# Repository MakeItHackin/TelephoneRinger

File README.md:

# TelephoneRinger

This is a work in progress.... updates and more links to come!
If you have any suggestions, plase let me know by opening an Issue

Project offered under Attribution 4.0 International (CC BY 4.0) License.
  
Not all phone use the same amount of voltage/current to ring.  Seems like the really old phones may require higher wattage and this board may or may not ring them.  
  
BILL OF MATERIALS:
Adafruit Feather (Tested with RP2040, M0 Express, 32u4 Basic, and ESP8266 HUZZAH)  
LEDs 5mm - 3  
RESISTORS 1k - 3  
RJ-11 JACK - 1  
DRV8871 MOTOR CONTROLLER - 1  (https://www.adafruit.com/product/3190)  
XL6019 BOOST CONVERTER - 1  
SWITCHES - 3  
6mm BUTTON - 1  
12mm BUTTON - 3  
  
OPTIONAL:  
RESISTORS 10k - 3  
SSD1306 OLED (i2c) - 1  
FEMALE HEADERS FOR MODULES  
MALE HEADERS FOR MODULES  
LIPO BATTERY - 1
ADAFRUIT FEATHER WING  
TELEPHONE RING GENERATOR PCB

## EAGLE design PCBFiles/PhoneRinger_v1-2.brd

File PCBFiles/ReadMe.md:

PCB Files are a work in progress!

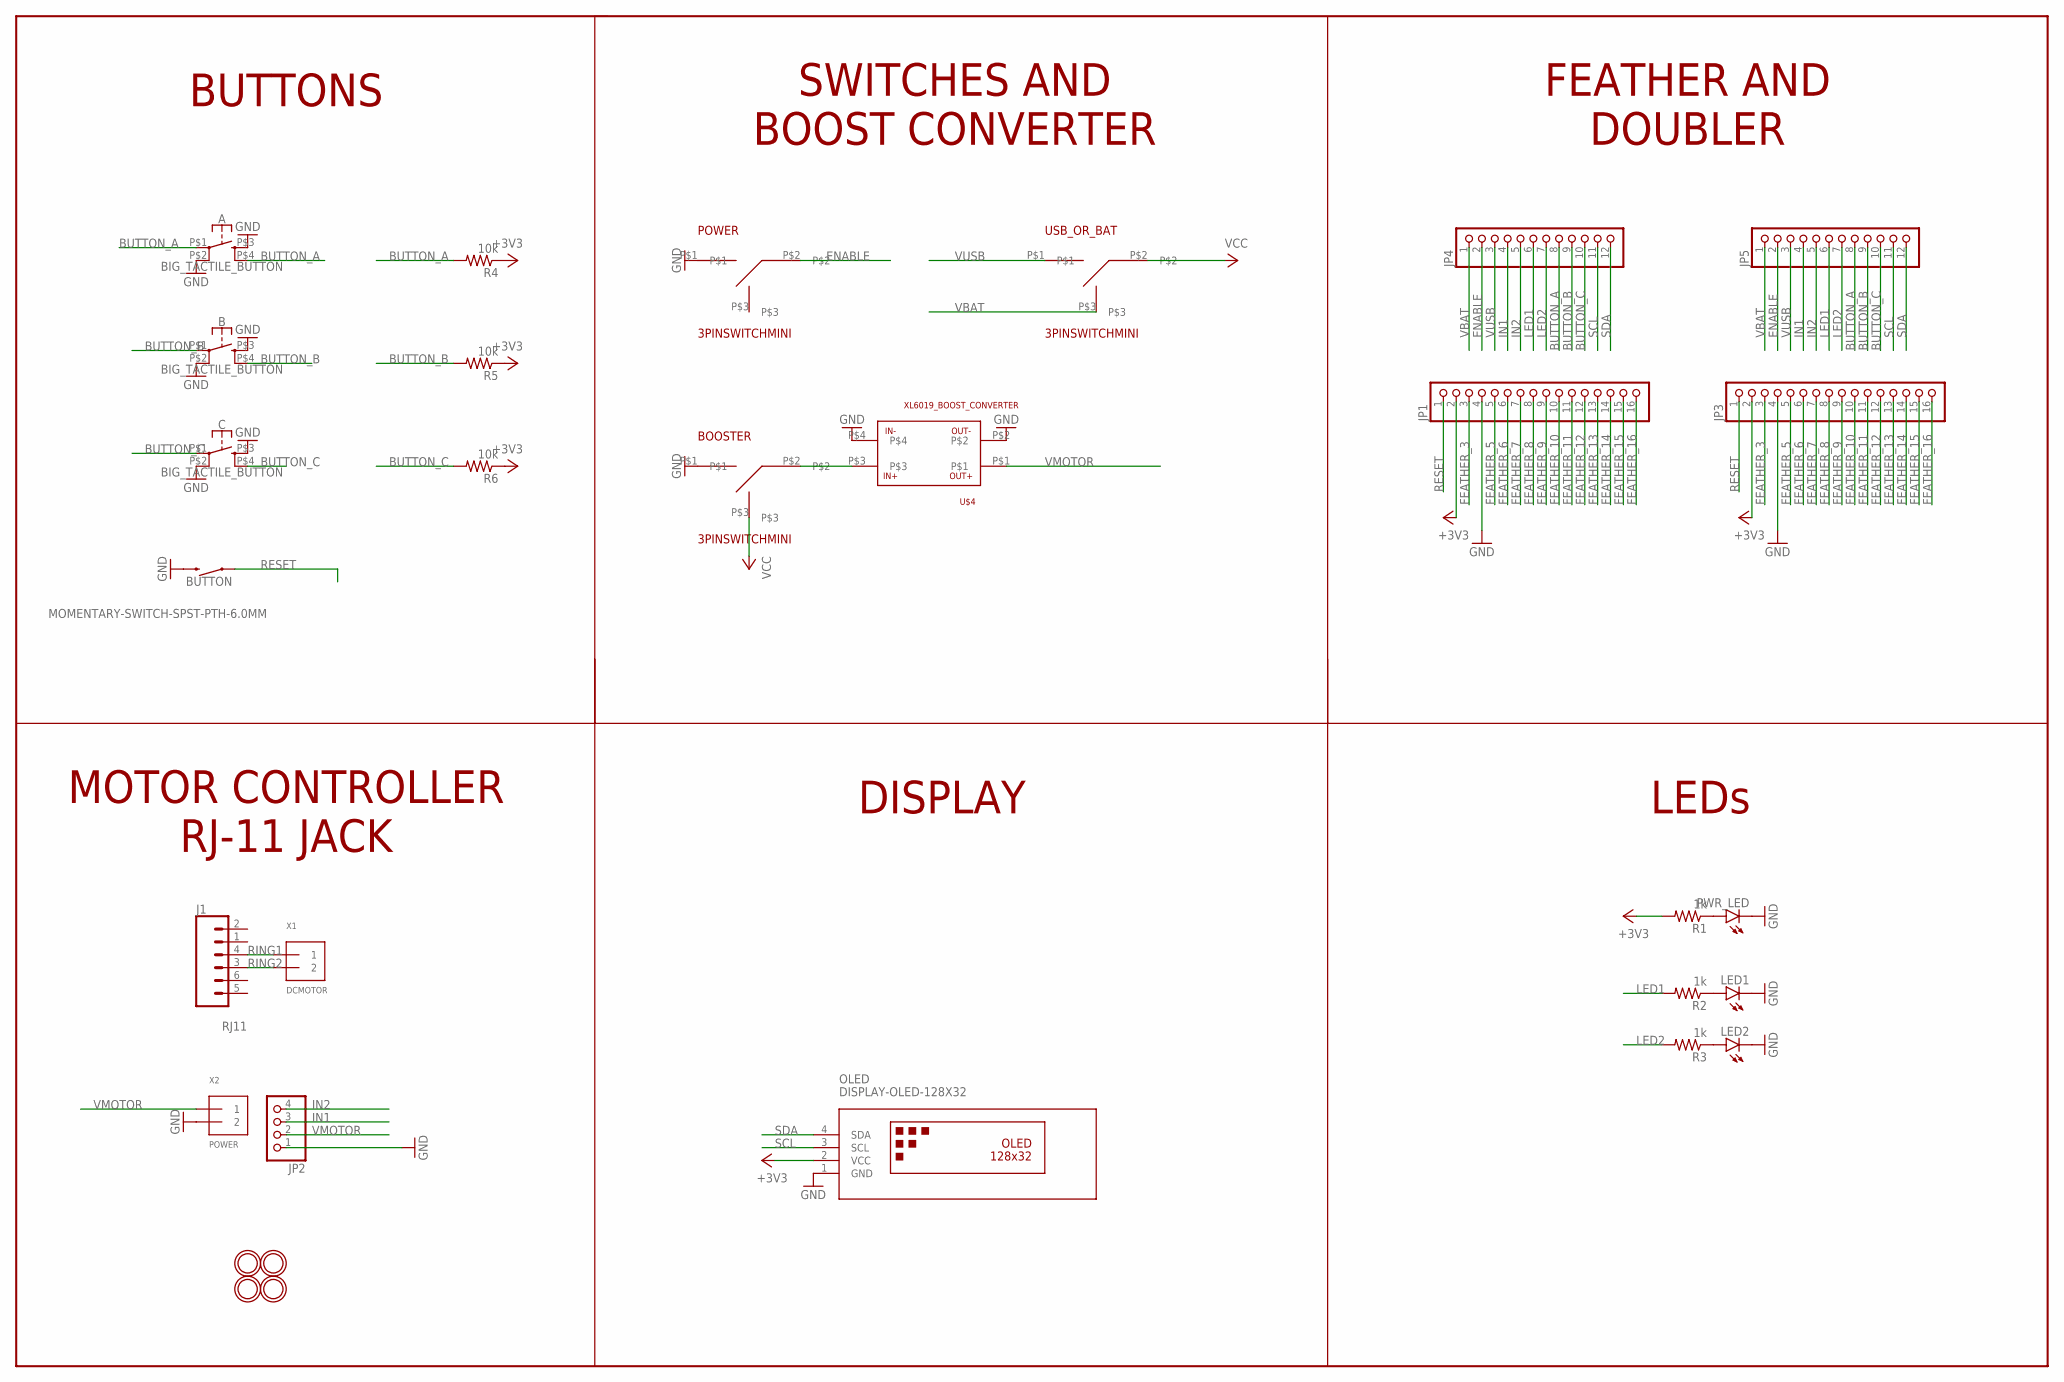
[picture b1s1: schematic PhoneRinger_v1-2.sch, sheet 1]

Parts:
A: BIG_TACTILE_BUTTON; BIG_TACTILE_BUTTON_FP
B: BIG_TACTILE_BUTTON; BIG_TACTILE_BUTTON_FP
BOOSTER: 3PINSWITCHMINI; 3PINMINI
BUTTON: MOMENTARY-SWITCH-SPST-PTH-6.0MM; TACTILE_SWITCH_PTH_6.0MM
C: BIG_TACTILE_BUTTON; BIG_TACTILE_BUTTON_FP
J1: RJ11; RJ11-6
JP1, JP3: HEADER-1X16_76MIL; 1X16_ROUND_76MIL
JP2: HEADER-1X476MIL; 1X04_ROUND_76
JP4, JP5: HEADER-1X1276MIL; 1X12_ROUND_76MIL
LED1, LED2: LED5MM
OLED: DISPLAY-OLED-128X32
POWER: 3PINSWITCHMINI; 3PINMINI
PWR_LED: LED5MM
R1, R2, R3: 1k; 0207/10
R4, R5, R6: 10k; 0207/10
U$4: XL6019_BOOST_CONVERTER; XL6019_FP
U$5, U$6, U$7, U$8: MICROBUILDER_MOUNTINGHOLE2.5_THICK; MICROBUILDER_MOUNTINGHOLE_2.5_PLATED_THICK
USB_OR_BAT: 3PINSWITCHMINI; 3PINMINI
X1: DCMOTOR; TERMBLOCK_1X2-3.5MM
X2: POWER; TERMBLOCK_1X2-3.5MM

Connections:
+3V3: JP1.2, JP3.2, OLED.2 (VCC), R1.2, R4.1, R5.1, R6.1
BUTTON_A: A.P$1 (1), A.P$4 (4), JP4.8, JP5.8, R4.2
BUTTON_B: B.P$1 (1), B.P$4 (4), JP4.9, JP5.9, R5.2
BUTTON_C: C.P$1 (1), C.P$4 (4), JP4.10, JP5.10, R6.2
ENABLE: JP4.2, JP5.2, POWER.P$2
FEATHER_3: JP1.3, JP3.3
FEATHER_5: JP1.5, JP3.5
FEATHER_6: JP1.6, JP3.6
FEATHER_7: JP1.7, JP3.7
FEATHER_8: JP1.8, JP3.8
FEATHER_9: JP1.9, JP3.9
FEATHER_10: JP1.10, JP3.10
FEATHER_11: JP1.11, JP3.11
FEATHER_12: JP1.12, JP3.12
FEATHER_13: JP1.13, JP3.13
FEATHER_14: JP1.14, JP3.14
FEATHER_15: JP1.15, JP3.15
FEATHER_16: JP1.16, JP3.16
GND: A.P$2 (2), A.P$3 (3), B.P$2 (2), B.P$3 (3), BOOSTER.P$1, BUTTON.3 (2), C.P$2 (2), C.P$3 (3), JP1.4, JP2.1, JP3.4, LED1.K (C), LED2.K (C), OLED.1 (GND), POWER.P$1, PWR_LED.K (C), U$4.P$2, U$4.P$4, X2.2
IN1: JP2.3, JP4.4, JP5.4
IN2: JP2.4, JP4.5, JP5.5
LED1: JP4.6, JP5.6, R2.2
LED2: JP4.7, JP5.7, R3.2
unnamed: PWR_LED.A, R1.1
unnamed: LED1.A, R2.1
unnamed: LED2.A, R3.1
unnamed: BOOSTER.P$2, U$4.P$3
RESET: BUTTON.1, JP1.1, JP3.1
RING1: J1.4, X1.1
RING2: J1.3, X1.2
SCL: JP4.11, JP5.11, OLED.3 (SCL)
SDA: JP4.12, JP5.12, OLED.4 (SDA)
VBAT: JP4.1, JP5.1, USB_OR_BAT.P$3
VCC: BOOSTER.P$3, USB_OR_BAT.P$2
VMOTOR: JP2.2, U$4.P$1, X2.1
VUSB: JP4.3, JP5.3, USB_OR_BAT.P$1

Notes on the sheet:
BUTTONS
SWITCHES AND BOOST CONVERTER
FEATHER AND DOUBLER
LEDs
DISPLAY
MOTOR CONTROLLER RJ-11 JACK

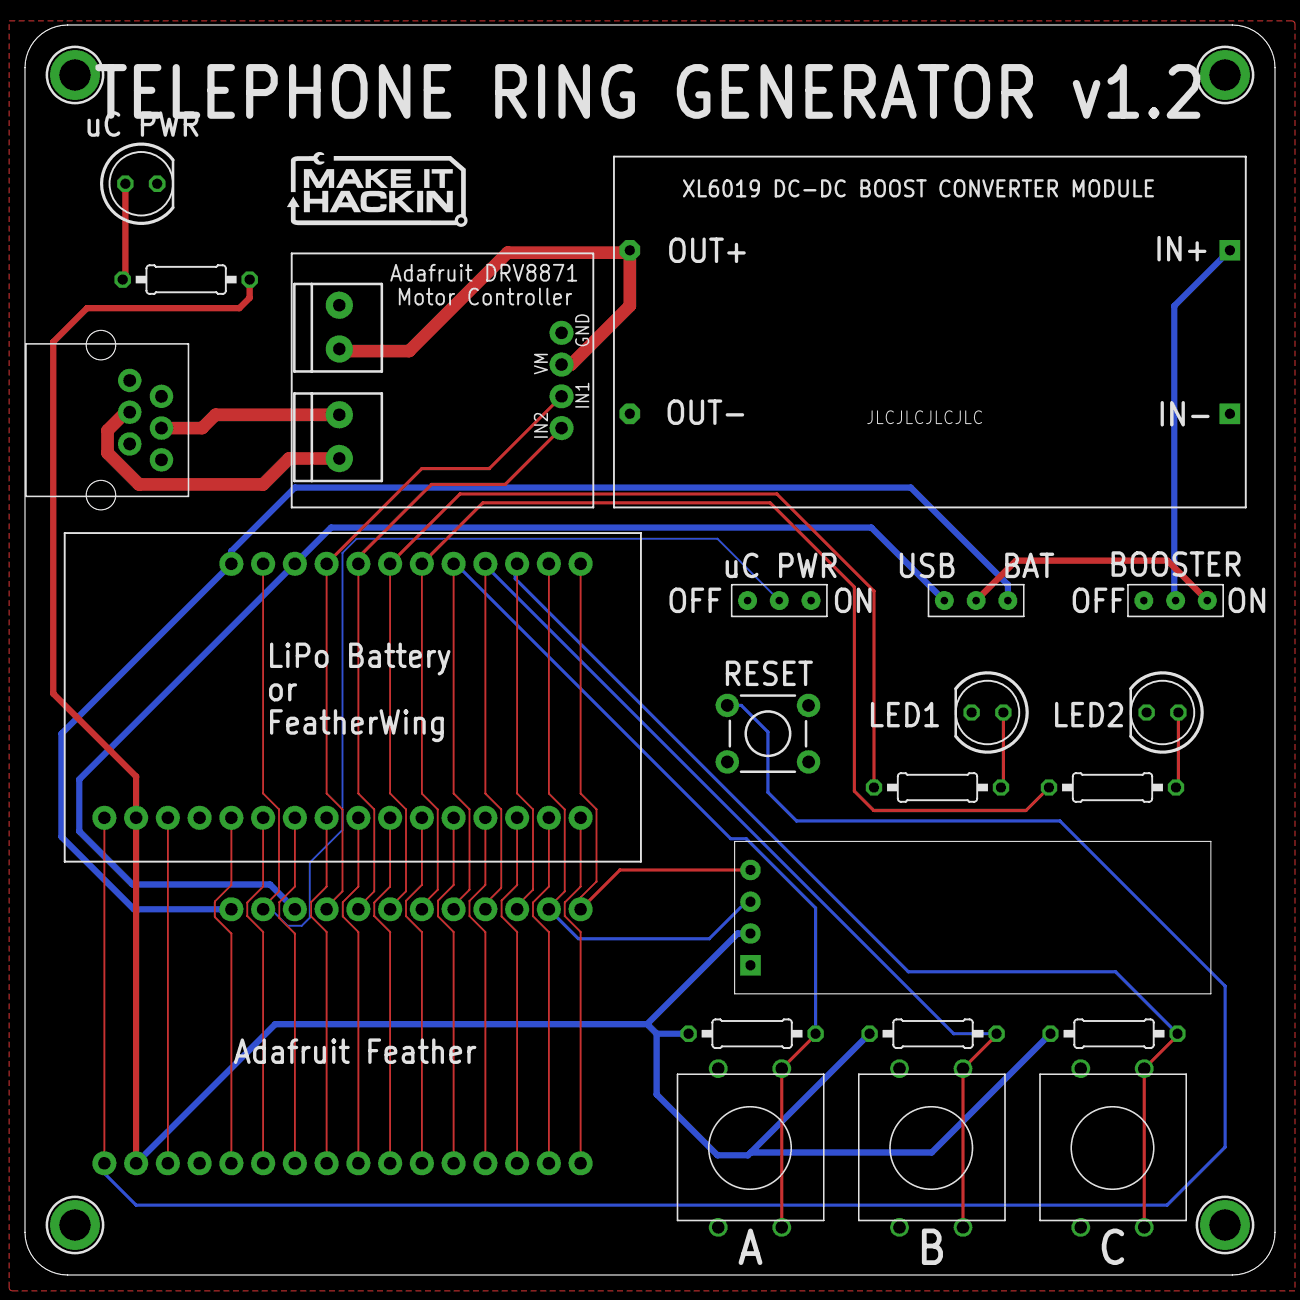
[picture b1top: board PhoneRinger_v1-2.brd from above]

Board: 2 copper layers, 100.0 x 100.0 mm, 30 parts (0 on the bottom side), 36 nets.

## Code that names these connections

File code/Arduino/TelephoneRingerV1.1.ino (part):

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
// PIN ASSIGNMENTS FOR A,B,C BUTTONS, MOTOR CONTROLLER, AND LEDS
#if defined(ESP8266)
  #define BUTTON_A  0
  #define BUTTON_B 16
  #define BUTTON_C  2
  #define IN1 14
  #define IN2 12
  #define LED1 13
  #define LED2 15
#elif defined(ESP32)
  #define BUTTON_A 15
  #define BUTTON_B 32
  #define BUTTON_C 14
  #define IN1 13
  #define IN2 12
  #define LED1 27
  #define LED2 33
#elif defined(ARDUINO_STM32_FEATHER)
  #define BUTTON_A PA15
  #define BUTTON_B PC7
  #define BUTTON_C PC5
  #define IN1 PB5
  #define IN2 PA13
  #define LED1 PA4
  #define LED2 PB4
#elif defined(TEENSYDUINO)
  #define BUTTON_A  4
  #define BUTTON_B  3
  #define BUTTON_C  8
  #define IN1 5
  #define IN2 6
  #define LED1 9
  #define LED2 10
#elif defined(ARDUINO_FEATHER52832)
  #define BUTTON_A 31
  #define BUTTON_B 30
  #define BUTTON_C 27
  #define IN1 16
  #define IN2 15
  #define LED1 7
  #define LED2 11
#else // 32u4, M0, M4, nrf52840 and 328p
  #define BUTTON_A  9
  #define BUTTON_B  6
  #define BUTTON_C  5
  #define IN1 13
  #define IN2 12
  #define LED1 11
  #define LED2 10
#endif


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  // SETTING UP PIN DIRECTION
  pinMode(IN1, OUTPUT);
  pinMode(IN2, OUTPUT);
  pinMode(LED1, OUTPUT);
  pinMode(LED2, OUTPUT);
  pinMode(BUTTON_A, INPUT_PULLUP);
  pinMode(BUTTON_B, INPUT_PULLUP);
  pinMode(BUTTON_C, INPUT_PULLUP);
  
  #if OLEDSCREEN == true
    if(!display.begin(SSD1306_SWITCHCAPVCC, 0x3C)) { // Address 0x3C for 128x32
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

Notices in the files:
code/Arduino/TelephoneRingerV1.1.ino:
BSD license, check license.txt for more information
parts and their libraries:
microbuilder: This work is placed in the public domain, and may be freely used for commercial and non-commercial work with the following conditions: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
